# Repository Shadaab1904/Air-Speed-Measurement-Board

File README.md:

# Air-Speed-Measurement-Board
This project is a custom-designed PCB that integrates a **Sensirion SDP810 differential pressure sensor** with an **STM32F030F4Px microcontroller**. The board is designed for use in airspeed measurement applications, such as on drones and UAVs. It measures differential pressure via I²C, applies onboard filtering, converts it into airspeed (in m/s), and provides the result via an SPI interface to a master controller. An **interrupt pin** signals the availability of new data.

## 📦 Overview

- **Sensor**: Sensirion SDP810-500PA (differential pressure sensor)
- **Microcontroller**: STM32F030F4Px (ARM Cortex-M0)
- **Power**: 5V input with onboard 3.3V regulation
- **Interfaces**:
  - I²C (sensor side)
  - SPI (to master controller)
  - Read Interrupt Pin (signals new data ready)
  - SWD (for programming/debugging)
 
 ## 🎯 Purpose

This board acts as an **airspeed signal processing unit**. It reads differential pressure caused by the difference between total and static air pressure (using a pitot tube setup), computes the **dynamic pressure**, and derives the **airspeed** using Bernoulli’s principle.

## 🧠 Functional Description

### 1. **Sensor Interface (I²C)**
- The STM32 communicates with the SDP810 sensor using I²C.
- The sensor provides differential pressure readings in Pascal (Pa).

### 2. **Signal Processing**
- Raw pressure readings are digitally filtered.
- The airspeed \( v \) is calculated using:

v = sqrt 2. Delta P / rho
where:
- Delta P = differential pressure in Pa
- rhO = air density (typically 1.225 kg/m³ at sea level)

### 3. **Data Output (SPI + Interrupt)**
- Filtered airspeed data is provided to an SPI master.
- An interrupt output toggles to notify the master of new data availability.

## 🔧 Key Components
- STM32F030F4Px: ARM Cortex-M0 MCU
- SDP810-500PA: Differential pressure sensor with I²C output
- HT75xx-1 (SOT89): Low dropout 3.3V voltage regulator
- B5819W: Reverse polarity protection diode
- TVS Diode: ESD protection on power lines
- Crystal. External clock source for STM32
- Conn_01x10_Pin: Main interface header
- Capacitors, Resistors: Decoupling, pull-ups, filtering
- Status Indicator: Optional debug/status indicator
- Ferrite Bead: Noise suppression on power line

## 📐 Pin Interface 

- VCC (5V): Input power (to LDO regulator)
- GND: Ground
- SWDIO: SWD programming interface
- SWCLK: SWD clock
- SPI_MISO: SPI Slave Output (to master)
- SPI_MOSI: SPI Slave Input (from master)
- SPI_SCK: SPI clock
- SPI_CS: Chip Select
- INT_OUT: Interrupt pin (new data ready)
- GND: Ground

## ⚡ Power and Programming
### 🔋 Power Supply

- Supply 5V through pin 1.
- The HT75xx LDO steps it down to 3.3V for STM32 and sensor.

### 🧠 Programming (SWD)

- Use **ST-Link V2** or equivalent SWD debugger:
-  STM32 Pin | ST-Link Pin
-  SWDIO     | SWDIO
-  SWCLK     | SWCLK
-  GND       | GND
-  NRST      | NRST
- 3.3V (ref) | Vcc

## 📈 Applications

- Fixed-wing drone airspeed measurement
- Feedback loop for fan/blower control
- Wind tunnel experiments
- HVAC airflow monitoring

## 📂 Project structure
- `Pressure sensor.kicad_sch` – Schematic file
- `Pressure sensor_pcb` – PCB layout file
- `Pressure sensor_pro` – KiCad project file
- `STEP/` - Sensor 3D model
- `gerber/` – Gerber and drill files for fabrication
- `bom.csv` – Bill of Materials

- ## ⚙️ Tools
- Designed with [KiCad](https://kicad.org/)

- ## 📦 Fabrication
Use the files in the `gerber/` directory to order PCBs from manufacturers (e.g., JLCPCB etc.).

- ## 📄 License
MIT License – feel free to modify and use.

## 🙌 Contributions
Pull requests welcome! If you spot issues or have improvements, please open an issue or PR.

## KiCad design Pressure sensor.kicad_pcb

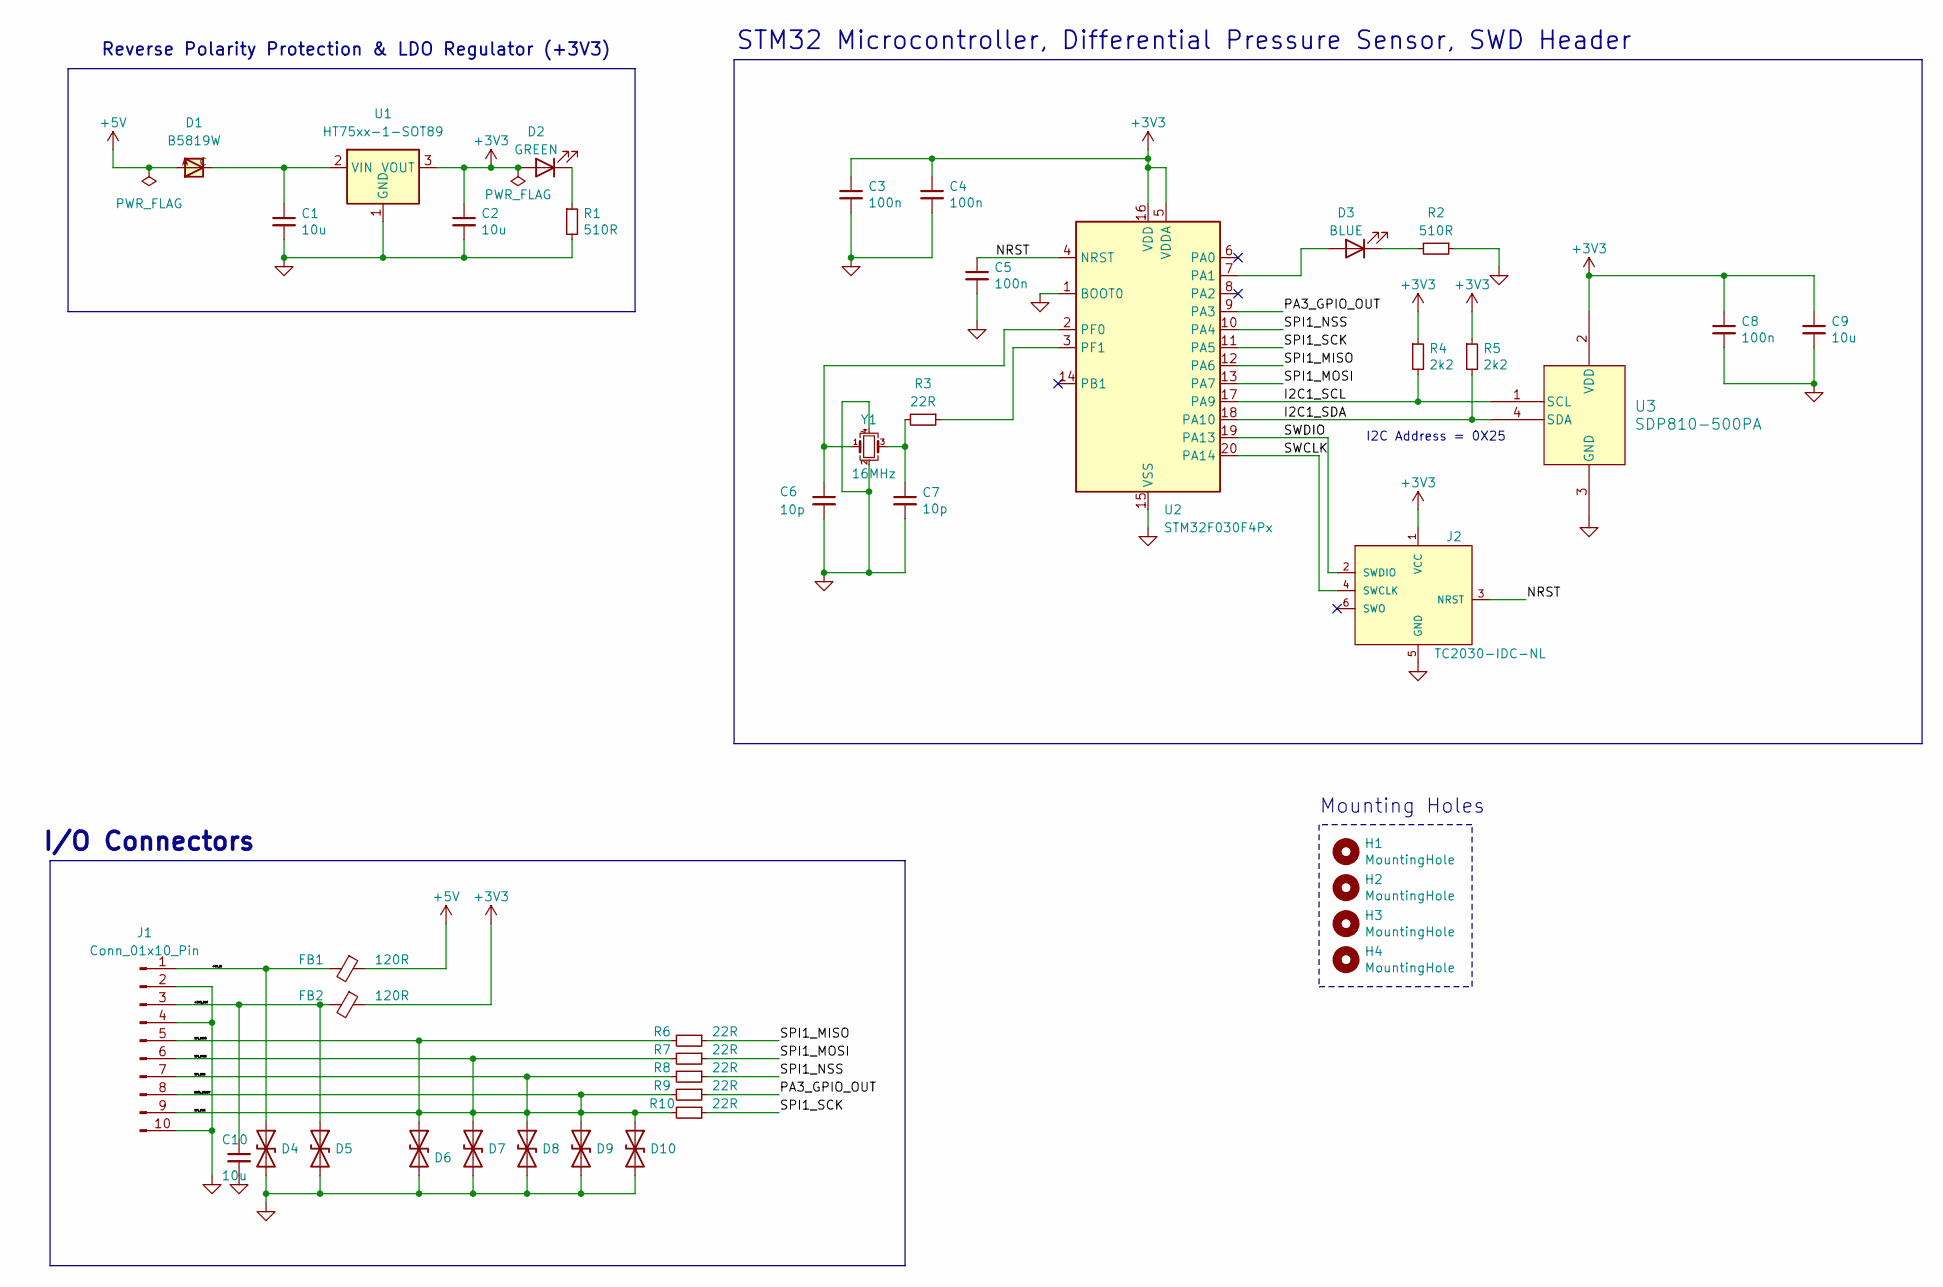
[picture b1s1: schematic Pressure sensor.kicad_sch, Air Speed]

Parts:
C1, C2, C9, C10: 10u; C_0805_2012Metric; LCSC Part # C15850
C3, C4, C5, C8: 100n; C_0402_1005Metric; LCSC Part # C1525
C6, C7: 10p; C_0402_1005Metric; LCSC Part # C32949
D1: B5819W; SOD123FL
D2: GREEN; LED_0603_1608Metric
D3: BLUE; LED_0603_1608Metric
D4, D5, D6, D7, D8, D9, D10: PESD5V0L1BA,115; D_SOD-323; LCSC Part # C85380
FB1, FB2: 120R; L_0603_1608Metric; LCSC Part # C85831
H1, H2, H3, H4: MountingHole; MountingHole_2.2mm_M2
J1: Conn_01x10_Pin; Molex_PicoBlade_53048-1010_1x10_P1.25mm_Horizontal
J2: TC2030-IDC-NL; TAG_TC2030-IDC-NL; PARTREV MS
R1, R2: 510R; R_0402_1005Metric; LCSC Part # C25123
R3, R6, R7, R8, R9, R10: 22R; R_0402_1005Metric; LCSC Part # C25092
R4, R5: 2k2; R_0402_1005Metric; LCSC Part # C25879
U1: HT75xx-1-SOT89; SOT-89-3
U2: STM32F030F4Px; TSSOP-20_4.4x6.5mm_P0.65mm
U3: SDP810-500PA; SDP81x_SEN
Y1: 16MHz; Crystal_SMD_3225-4Pin_3.2x2.5mm; LCSC Part # C13738

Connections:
+3V3: C2.1, C3.1, C4.1, C8.1, C9.1, D2.2 (A), FB2.1, J2.1 (VCC), R4.1, R5.1, U1.3 (VOUT), U2.5 (VDDA), U2.16 (VDD), U3.2 (VDD)
+5V: D1.A, FB1.1
/+3V3_OUT: C10.1, D5.1 (A1), FB2.2, J1.3
/+5V_IN: D4.1 (A1), FB1.2, J1.1
/DATA_READY: D6.1 (A1), D7.1 (A1), D8.1 (A1), D9.1 (A1), D10.1 (A1), J1.5, J1.6, J1.7, J1.8, J1.9, R6.2, R7.2, R8.2, R9.2, R10.2
/I2C1_SCL: R4.2, U2.17 (PA9), U3.1 (SCL)
/I2C1_SDA: R5.2, U2.18 (PA10), U3.4 (SDA)
/NRST: C5.1, J2.3 (NRST), U2.4 (NRST)
/PA3_GPIO_OUT: R9.1, U2.9 (PA3)
/SPI1_MISO: R6.1, U2.12 (PA6)
/SPI1_MOSI: R7.1, U2.13 (PA7)
/SPI1_NSS: R8.1, U2.10 (PA4)
/SPI1_SCK: R10.1, U2.11 (PA5)
/SWCLK: J2.4 (SWCLK), U2.20 (PA14)
/SWDIO: J2.2 (SWDIO), U2.19 (PA13)
GND: C1.2, C2.2, C3.2, C4.2, C5.2, C6.2, C7.2, C8.2, C9.2, C10.2, D4.2 (A2), D5.2 (A2), D6.2 (A2), D7.2 (A2), D8.2 (A2), D9.2 (A2), D10.2 (A2), J1.2, J1.4, J1.10, J2.5 (GND), R1.2, R2.1, U1.1 (GND), U2.1 (BOOT0), U2.15 (VSS), U3.3 (GND), Y1.2, Y1.4
unnamed: C7.1, R3.2, Y1.3
unnamed: D2.1 (K), R1.1
unnamed: D3.2 (A), U2.7 (PA1)
unnamed: D3.1 (K), R2.2
unnamed: C1.1, D1.C, U1.2 (VIN)
unnamed: C6.1, U2.2 (PF0), Y1.1
unnamed: R3.1, U2.3 (PF1)

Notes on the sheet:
I2C Address = 0X25
Mounting Holes
I/O Connectors
Reverse Polarity Protection & LDO Regulator (+3V3)
STM32 Microcontroller, Differential Pressure Sensor, SWD Header

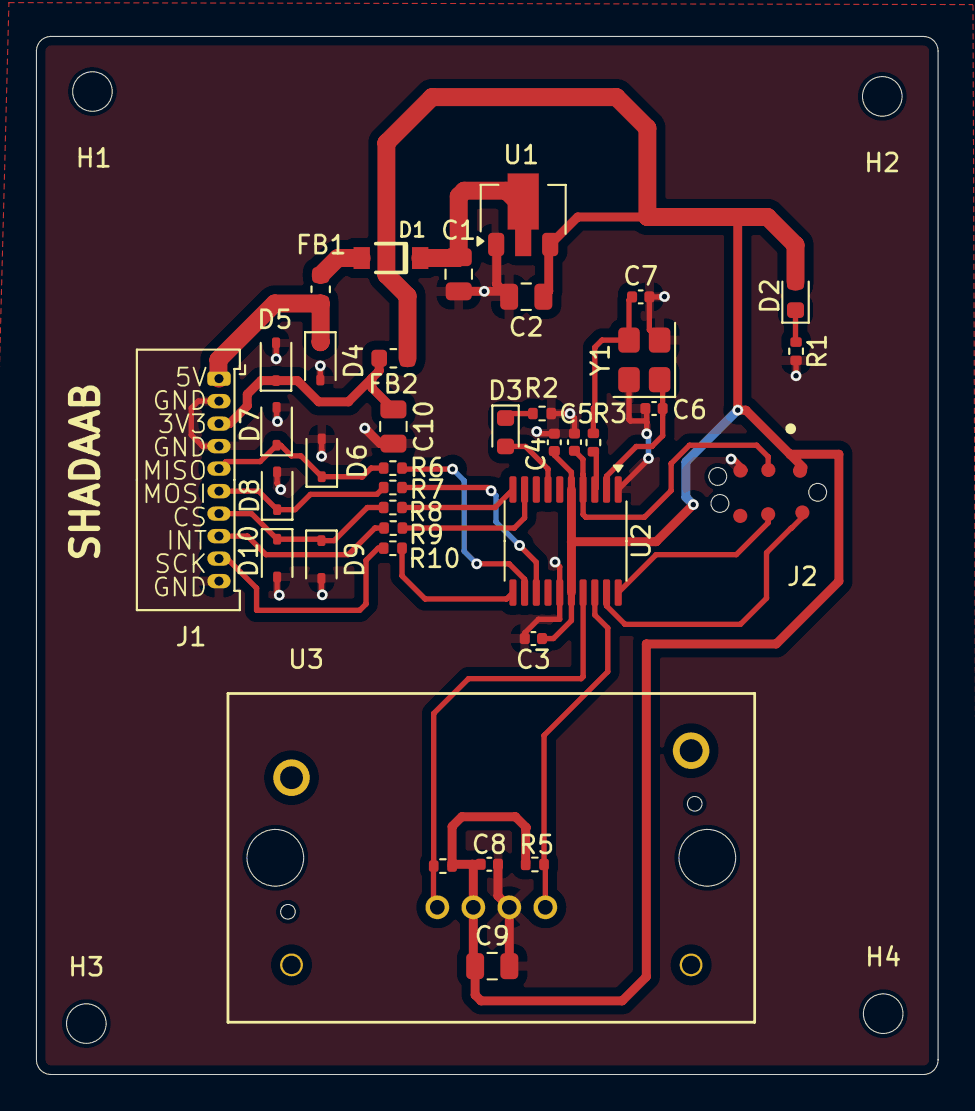
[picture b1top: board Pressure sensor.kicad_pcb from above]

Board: 2 copper layers, 50.1 x 57.7 mm, 42 parts (0 on the bottom side), 23 nets.

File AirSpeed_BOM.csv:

"Reference","Qty","Value","DNP","Exclude from BOM","Exclude from Board","Footprint","Datasheet"
"C1,C2,C9,C10","4","10u","","","","Capacitor_SMD:C_0805_2012Metric","~"
"C3,C4,C5,C8","4","100n","","","","Capacitor_SMD:C_0402_1005Metric","~"
"C6,C7","2","10p","","","","Capacitor_SMD:C_0402_1005Metric","~"
"D1","1","B5819W","","","","B5819W:SOD123FL",""
"D2","1","GREEN","","","","LED_SMD:LED_0603_1608Metric","~"
"D3","1","BLUE","","","","LED_SMD:LED_0603_1608Metric","~"
"D4,D5,D6,D7,D8,D9,D10","7","PESD5V0L1BA,115","","","","Diode_SMD:D_SOD-323","~"
"FB1,FB2","2","120R","","","","Inductor_SMD:L_0603_1608Metric","~"
"H1,H2,H3,H4","4","MountingHole","","","","MountingHole:MountingHole_2.2mm_M2","~"
"J1","1","Conn_01x10_Pin","","","","Connector_Molex:Molex_PicoBlade_53048-1010_1x10_P1.25mm_Horizontal","~"
"J2","1","TC2030-IDC-NL","","","","TC2030-IDC-NL:TAG_TC2030-IDC-NL",""
"R1,R2","2","510R","","","","Resistor_SMD:R_0402_1005Metric","~"
"R3,R6,R7,R8,R9,R10","6","22R","","","","Resistor_SMD:R_0402_1005Metric","~"
"R4,R5","2","2k2","","","","Resistor_SMD:R_0402_1005Metric","~"
"U1","1","HT75xx-1-SOT89","","","","Package_TO_SOT_SMD:SOT-89-3","https://www.holtek.com/documents/10179/116711/HT75xx-1v250.pdf"
"U2","1","STM32F030F4Px","","","","Package_SO:TSSOP-20_4.4x6.5mm_P0.65mm","https://www.st.com/resource/en/datasheet/stm32f030f4.pdf"
"U3","1","SDP810-500PA","","","","CustomFootprints:SDP81x_SEN","SDP810-500PA"
"Y1","1","16MHz","","","","Crystal:Crystal_SMD_3225-4Pin_3.2x2.5mm","~"
